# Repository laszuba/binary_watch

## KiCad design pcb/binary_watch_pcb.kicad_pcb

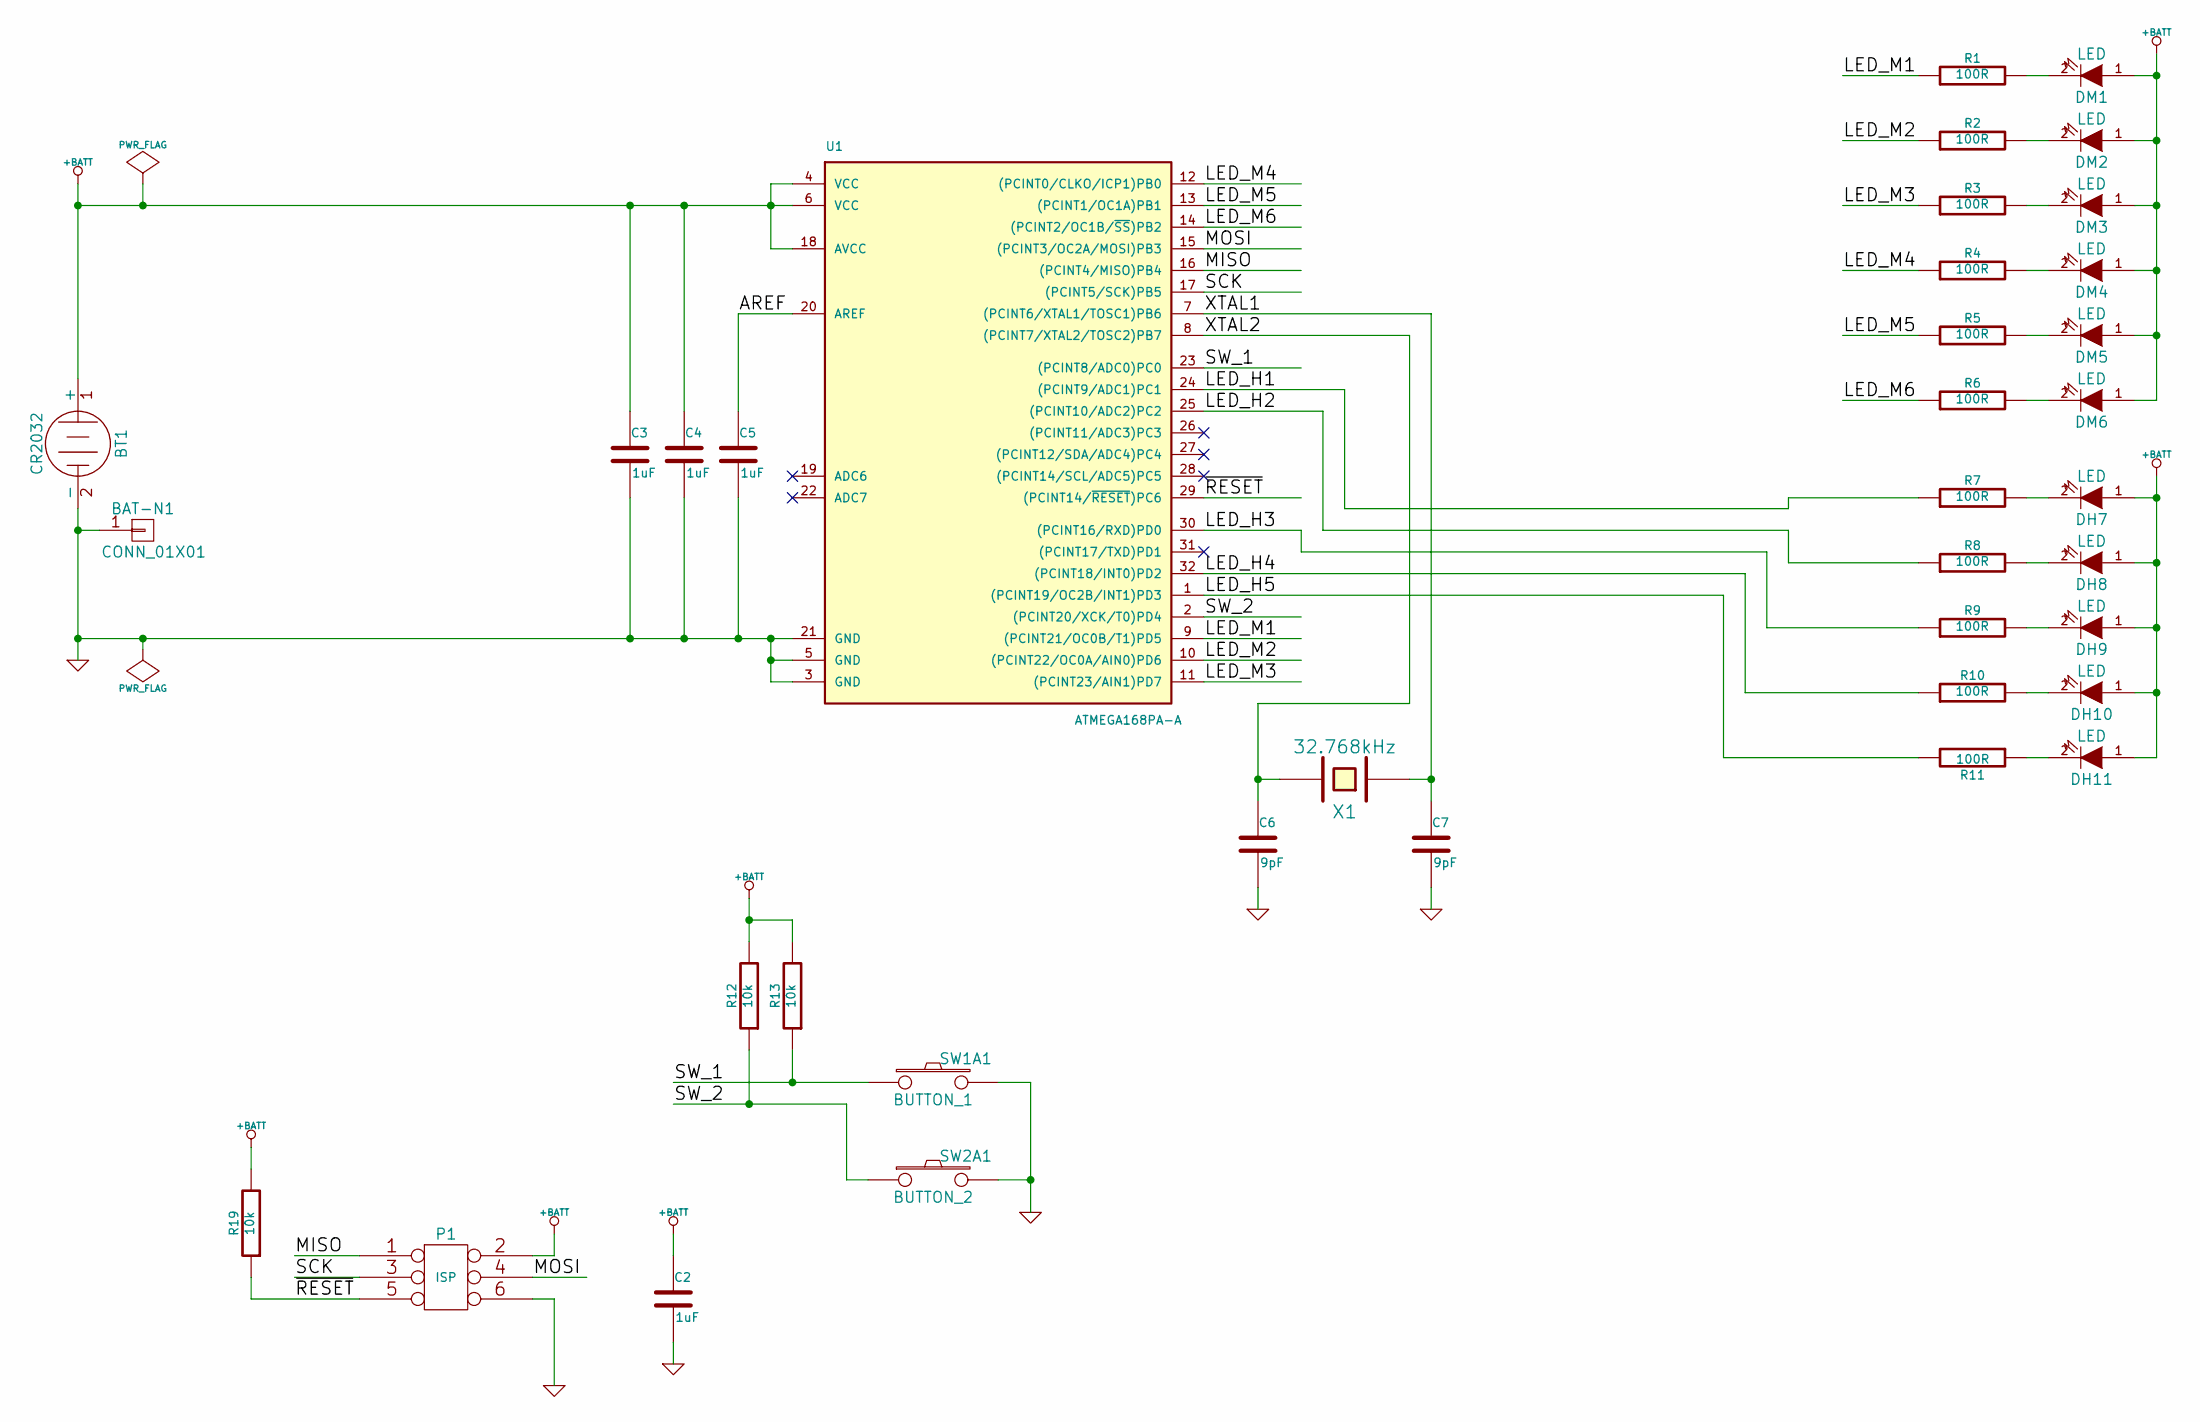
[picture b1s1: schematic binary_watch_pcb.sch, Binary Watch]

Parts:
BAT-N1: CONN_01X01
BT1: CR2032; CR2032_MPD; Manufacturer P/N BU2032SM-HD-G
C2, C3, C4, C5: 1uF; C_0603; Manufacturer P/N LMK107B7105KA-T
C6, C7: 9pF; C_0402; Manufacturer P/N GRM1555C1H9R0BA01D
DH7, DH8, DH9, DH10, DH11: LED; LED-0805
DM1, DM2, DM3, DM4, DM5, DM6: LED; LED-0805
P1: ISP; Pin_Header_Straight_2x03
R1, R2, R3, R4, R5, R6, R7, R8, R9, R10, R11: 100R; R_0402
R12, R13, R19: 10k; R_0402
SW1A1: BUTTON_1; EVQ-P7C01P; Manufacturer P/N EVQ-P7C01P
SW2A1: BUTTON_2; EVQ-P7C01P; Manufacturer P/N EVQ-P7C01P
U1: ATMEGA168PA-A; TQFP-32
X1: 32.768kHz; XTAL_ABS07; Manufacturer P/N ABS07-32.768KHZ-9-T

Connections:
+BATT: BT1.1 (+), C2.1, C3.1, C4.1, DH7.1 (A), DH8.1 (A), DH9.1 (A), DH10.1 (A), DH11.1 (A), DM1.1 (A), DM2.1 (A), DM3.1 (A), DM4.1 (A), DM5.1 (A), DM6.1 (A), P1.2, R12.2, R13.2, R19.2, U1.4 (VCC), U1.6 (VCC), U1.18 (AVCC)
/AREF: C5.1, U1.20 (AREF)
/LED_H1: R7.1, U1.24 ((PCINT9/ADC1)PC1)
/LED_H2: R8.1, U1.25 ((PCINT10/ADC2)PC2)
/LED_H3: R9.1, U1.30 ((PCINT16/RXD)PD0)
/LED_H4: R10.1, U1.32 ((PCINT18/INT0)PD2)
/LED_H5: R11.2, U1.1 ((PCINT19/OC2B/INT1)PD3)
/LED_M1: R1.1, U1.9 ((PCINT21/OC0B/T1)PD5)
/LED_M2: R2.1, U1.10 ((PCINT22/OC0A/AIN0)PD6)
/LED_M3: R3.1, U1.11 ((PCINT23/AIN1)PD7)
/LED_M4: R4.1, U1.12 ((PCINT0/CLKO/ICP1)PB0)
/LED_M5: R5.1, U1.13 ((PCINT1/OC1A)PB1)
/LED_M6: R6.1, U1.14 ((PCINT2/OC1B/~SS~)PB2)
/MISO: P1.1, U1.16 ((PCINT4/MISO)PB4)
/MOSI: P1.4, U1.15 ((PCINT3/OC2A/MOSI)PB3)
/SCK: P1.3, U1.17 ((PCINT5/SCK)PB5)
/SW_1: R13.1, SW1A1.1, U1.23 ((PCINT8/ADC0)PC0)
/SW_2: R12.1, SW2A1.1, U1.2 ((PCINT20/XCK/T0)PD4)
/XTAL1: C7.1, U1.7 ((PCINT6/XTAL1/TOSC1)PB6), X1.1
/XTAL2: C6.1, U1.8 ((PCINT7/XTAL2/TOSC2)PB7), X1.2
/~RESET: P1.5, R19.1, U1.29 ((PCINT14/~RESET~)PC6)
GND: BAT-N1.1, BT1.2 (-), C2.2, C3.2, C4.2, C5.2, C6.2, C7.2, P1.6, SW1A1.2, SW2A1.2, U1.3 (GND), U1.5 (GND), U1.21 (GND)
unnamed: DH7.2 (K), R7.2
unnamed: DH8.2 (K), R8.2
unnamed: DH9.2 (K), R9.2
unnamed: DH10.2 (K), R10.2
unnamed: DH11.2 (K), R11.1
unnamed: DM1.2 (K), R1.2
unnamed: DM2.2 (K), R2.2
unnamed: DM3.2 (K), R3.2
unnamed: DM4.2 (K), R4.2
unnamed: DM5.2 (K), R5.2
unnamed: DM6.2 (K), R6.2

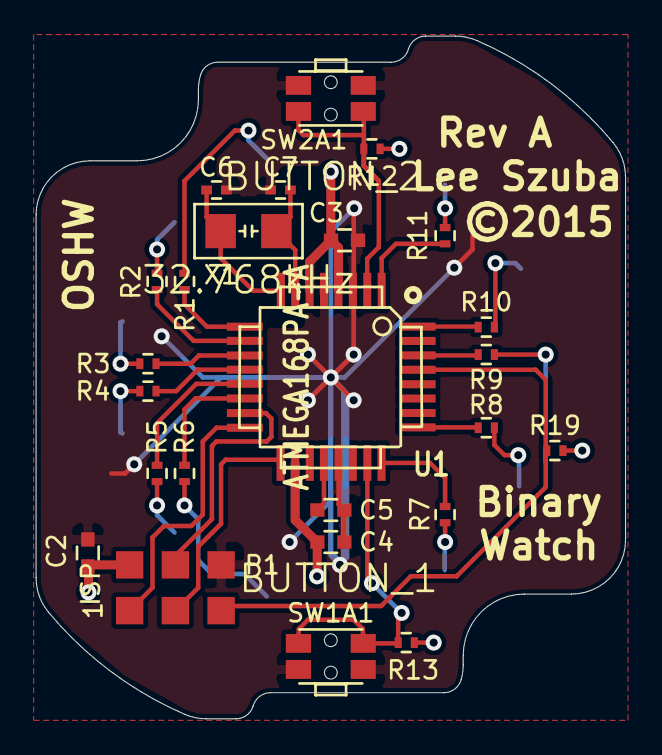
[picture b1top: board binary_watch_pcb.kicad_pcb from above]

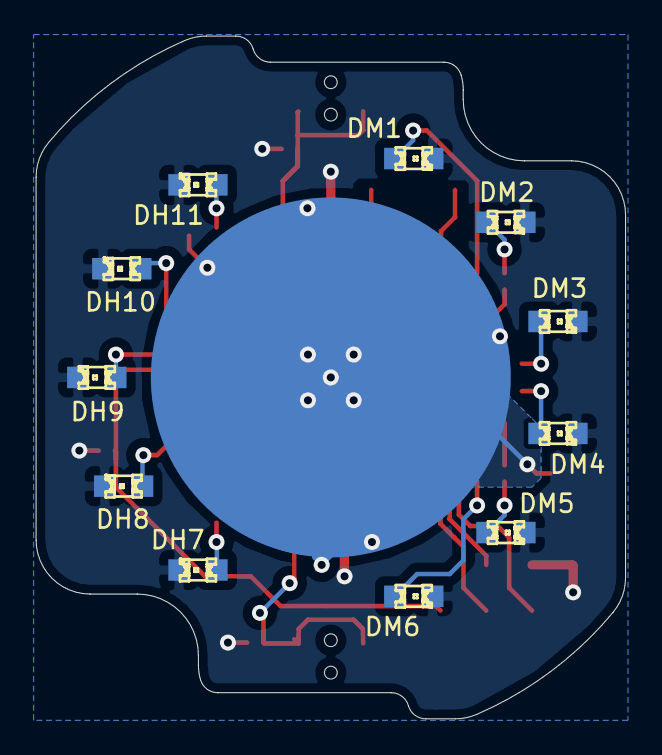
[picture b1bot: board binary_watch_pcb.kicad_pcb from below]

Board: 2 copper layers, 32.7 x 37.9 mm, 37 parts (12 on the bottom side), 33 nets.

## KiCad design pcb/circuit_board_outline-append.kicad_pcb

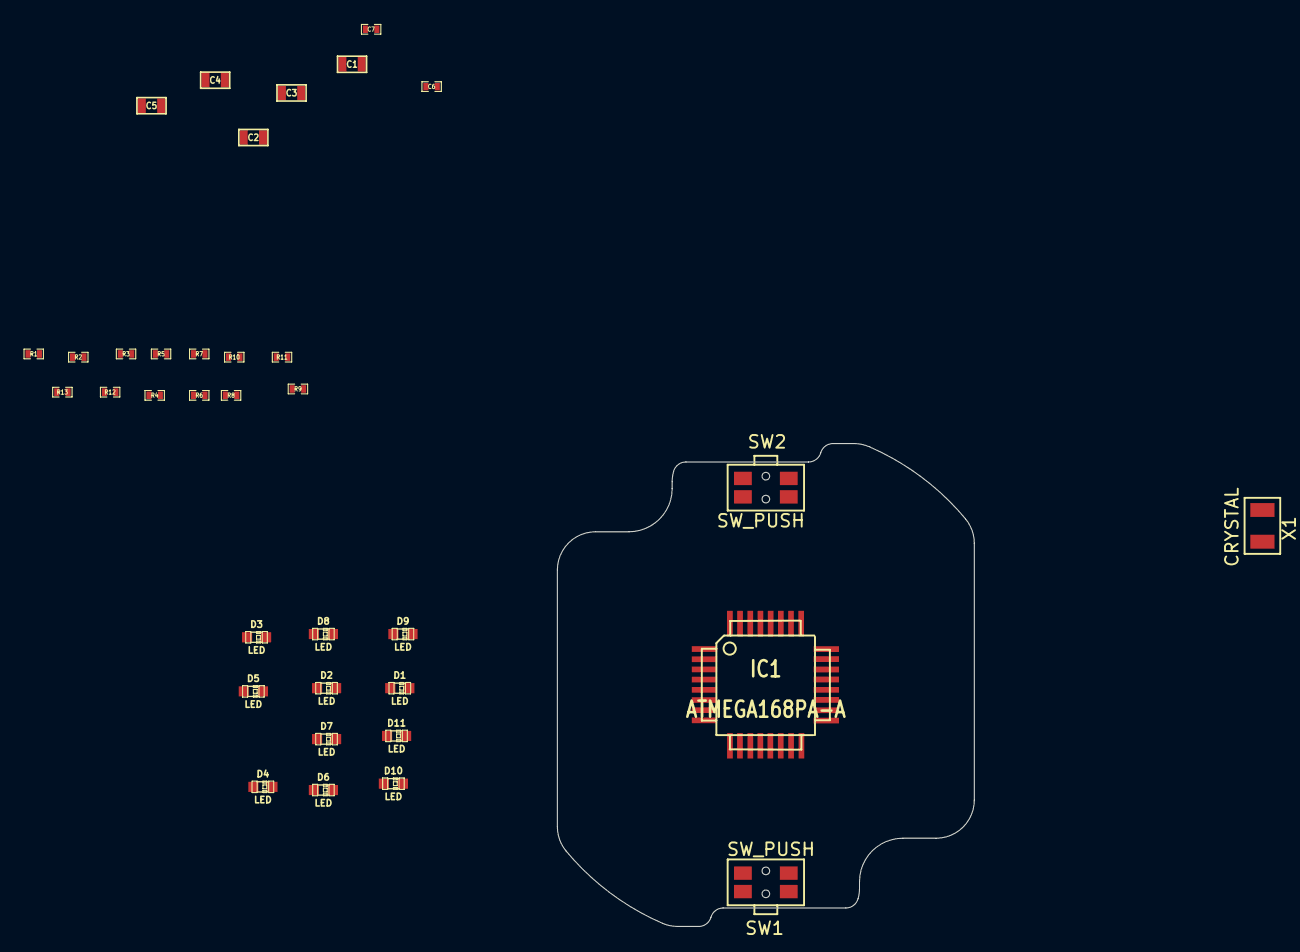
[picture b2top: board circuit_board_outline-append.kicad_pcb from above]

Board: 2 copper layers, 32.7 x 37.9 mm, 35 parts (0 on the bottom side), 29 nets, no tracks yet.

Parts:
C1, C2, C3, C4, C5: 1uF; SM0603
C6, C7: C; SM0402
D1, D2, D3, D4, D5, D6, D7, D8, D9, D10, D11: LED; LED-0603
IC1: ATMEGA168PA-A; TQFP32
R1, R2, R3, R4, R5, R6, R7, R8, R9, R10, R11: 100R; SM0402
R12, R13: 10k; SM0402
SW1, SW2: SW_PUSH; EVQP7
X1: CRYSTAL; ADS07

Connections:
+3.3V: C1.1, C2.1, C3.1, C4.1, IC1.4, IC1.6, IC1.18, R1.2, R2.2, R3.2, R4.2, R5.2, R6.2, R7.2, R8.2, R9.2, R10.2, R11.2, R12.2, R13.2
GND: C1.2, C2.2, C3.2, C4.2, C5.2, C6.2, C7.2, IC1.3, IC1.5, IC1.21, SW1.2, SW2.2
unnamed: D9.2, IC1.25
unnamed: D3.2, IC1.14
unnamed: D4.2, IC1.15
unnamed: D5.2, IC1.16
unnamed: D6.1, R6.1
unnamed: D6.2, IC1.17
unnamed: D7.1, R7.1
unnamed: D7.2, IC1.23
unnamed: D8.1, R8.1
unnamed: D8.2, IC1.24
unnamed: D9.1, R9.1
unnamed: D2.2, IC1.13
unnamed: D10.1, R10.1
unnamed: D10.2, IC1.26
unnamed: D11.1, R11.1
unnamed: D11.2, IC1.27
unnamed: C5.1, IC1.20
unnamed: D1.1, R1.1
unnamed: IC1.10, R13.1, SW1.1
unnamed: IC1.11, R12.1, SW2.1
unnamed: D1.2, IC1.12
unnamed: D2.1, R2.1
unnamed: D3.1, R3.1
unnamed: D4.1, R4.1
unnamed: D5.1, R5.1
unnamed: C6.1, IC1.8, X1.2
unnamed: C7.1, IC1.7, X1.1

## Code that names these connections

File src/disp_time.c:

/******************************************************************************
 *
 * File: disp_time.c
 * Author: Lee Szuba
 * Created: Sept. 2014
 *
 * Usage:
 *		Contains functions to display time on binary watch LEDs
 *
 * See the LICENCE file included with this software for copyright information
 *
 ******************************************************************************/

#include <avr/io.h>

#include "disp_time.h"
#include "init.h"
#include "macros.h"


// LEDS
// 
// Minutes:
//	M1 -> bit0 -> PD5
//	M2 -> bit1 -> PD6
//	M3 -> bit2 -> PD7
//	M4 -> bit3 -> PB0
//	M5 -> bit4 -> PB1
//	M6 -> bit5 -> PB2
//
// Hours:
//	H1 -> bit0 -> PC1
//	H2 -> bit1 -> PC2
//	H3 -> bit2 -> PD0
//	H4 -> bit3 -> PD2
//	H5 -> bit4 -> PD3
//
// All are active low

volatile static enabled_t disp_mins_enable = DISABLE;
volatile static enabled_t disp_hours_enable = DISABLE;

/**************************************************
 * Public Functions
 **************************************************/

void disp_time(uint8_t pwm_state) {
	uint8_t hours_leds = 0;
	uint8_t mins_leds = 0;

	if (pwm_state == ENABLE) {
		if (disp_mins_enable == ENABLE) mins_leds = my_time.mins;
		if (disp_hours_enable == ENABLE) hours_leds = my_time.hours;
	}

	// Make sure all the LEDs are off
	PORTB |= (1 << PB2) | (1 << PB1) | (1 << PB0);
	PORTC |= (1 << PC2) | (1 << PC1);
	PORTD |= (1 << PD7) | (1 << PD6) | (1 << PD5) | (1 << PD3) | (1 << PD2) | (1 << PD0);

	// Map time in structure to binary time on LEDs
	PORTC &=  ~((0b00000011 & hours_leds) << 1);
	PORTD &= ~(((0b00000100 & hours_leds) >> 2)
	         | ((0b00011000 & hours_leds) >> 1)
	         | ((0b00000111 & mins_leds ) << 5));
	PORTB &=  ~((0b00111000 & mins_leds ) >> 3);

	return;
}

void mins_off() {
	disp_mins_enable = DISABLE;
	return;
}

void hours_off() {
	disp_hours_enable = DISABLE;
	return;
}

void disp_off() {
	disp_hours_enable = DISABLE;
	disp_mins_enable = DISABLE;
}

void disp_on() {
	disp_hours_enable = ENABLE;
	disp_mins_enable = ENABLE;
	return;
}

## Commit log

2014-10-02 add pcb files
2014-10-12 Update to latest kicad version, create footprints.
2014-10-12 Move to 5x5 board for cost
2014-11-05 Add new dev pcb files from nightly build of kicad
2014-11-14 Finish dev schematic and layout, create gerbers to send to manufacture
2014-12-07 Add makefile, get first running code to PWM LEDs
2014-12-07 Remove unneeded kicad files (backups, etc.)
2014-12-07 Begin adding timing and time set logic
2014-12-08 Move debounce logic to a new file.
2014-12-12 Refactor debouncing code to hopefully be a little more durable across interrupts
2015-02-26 Finish debouncer, get main state machine working, add main.h
2015-05-22 Gen fab outputs, pdfs, and finish final routing.

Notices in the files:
pcb/binary_watch_pcb.kicad_pcb:
©2015
